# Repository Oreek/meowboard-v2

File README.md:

# ~meowpad~ Meowboard
A custom keyboard made with 62 keys and a rotary encoder. Used Kicad for the Schematics and PCB and also used OnShape for the Bottom Case.

---
## DEVLOGS
[DAY 1] Initial setup: ~creating a hackpad in EasyEDA~ Changed my mind, creating an entire 62 key keyboard.

0 hours

[DAY 1] Created complete schematic for the meowboard. Working on the PCB starting now.

2hr 30 mins
---

[DAY 1] Finally finished creating the PCB including the route tracing.

2hr 45mins
---

[DAY 1] Uhh so ig this is it. I've created the bottom plate for the PCB in onshape. Yeah, I did not make a top plate and didn't add any mounting holes because I wanted to hot glue the pcb to the bottom plate and i find the top plate pretty useless (personal preference ig)

1 hr 15 mins
---

With this, I think I'm done with the designing part of the project..? the rest I can only do with the hardware itself.

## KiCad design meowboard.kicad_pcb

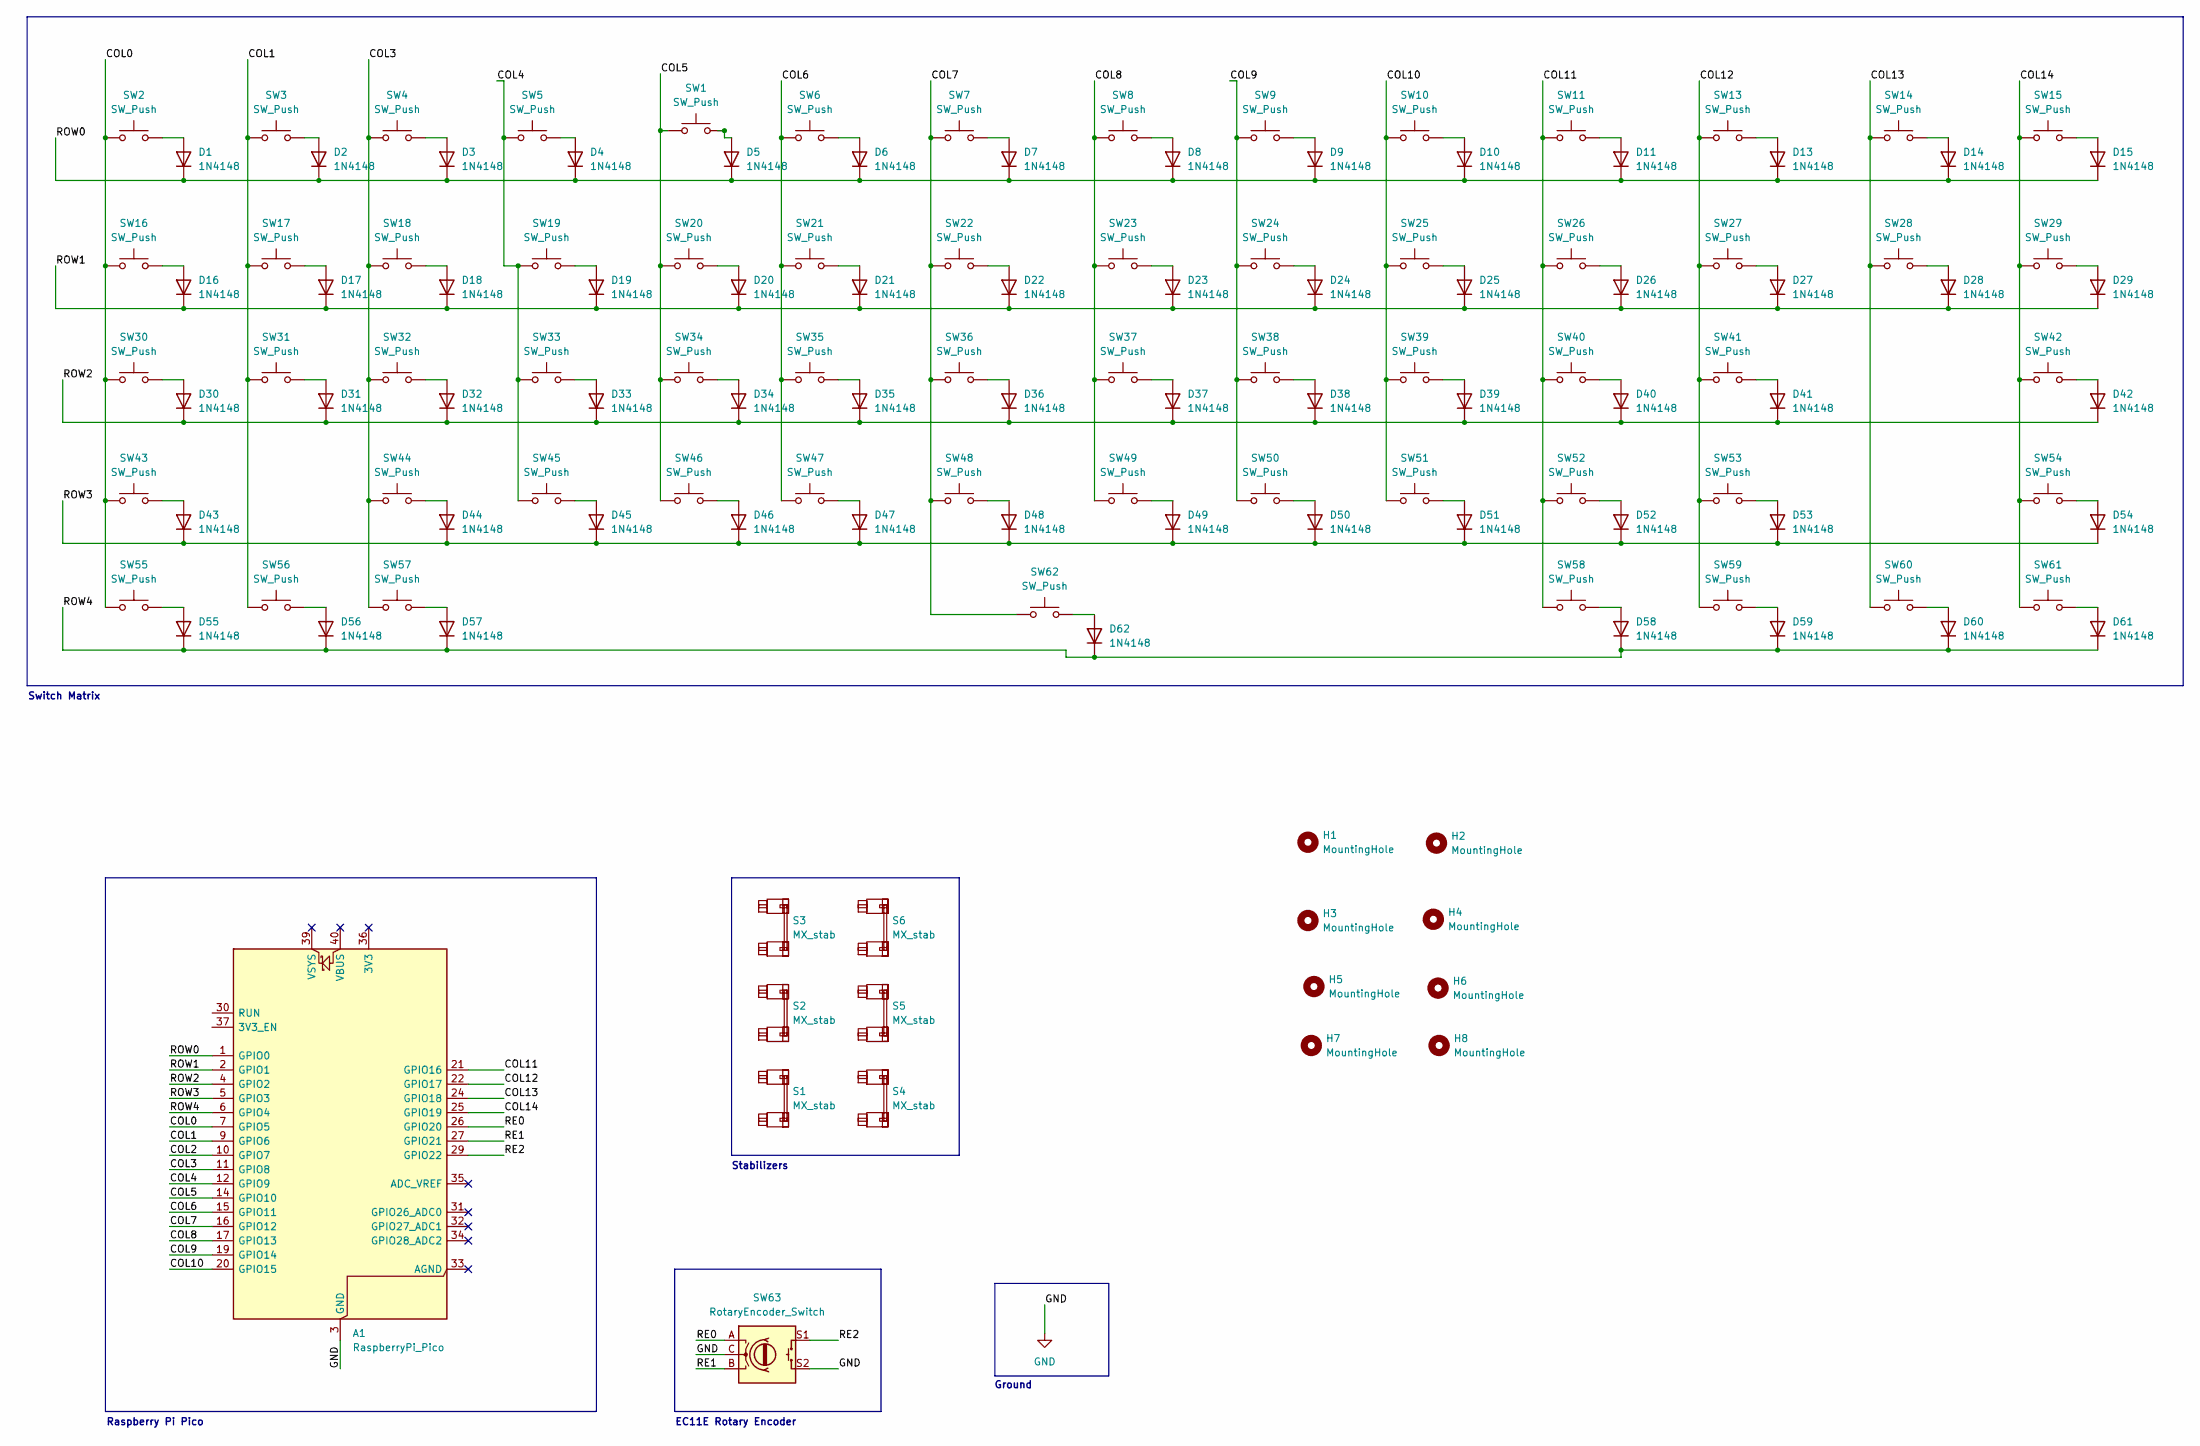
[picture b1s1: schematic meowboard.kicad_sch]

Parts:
A1: RaspberryPi_Pico; RaspberryPi_Pico_Common_Unspecified
D1, D2, D3, D4, D5, D6, D7, D8, D9, D10, D11, D13, D14, D15, D16, D17, D18, D19, D20, D21, D22, D23, D24, D25, D26, D27, D28, D29, D30, D31, D32, D33, D34, D35, D36, D37, D38, D39, D40, D41, D42, D43, D44, D45, D46, D47, D48, D49, D50, D51, D52, D53, D54, D55, D56, D57, D58, D59, D60, D61, D62: 1N4148; D_DO-35_SOD27_P7.62mm_Horizontal
H1, H2, H3, H4, H5, H6, H7, H8: MountingHole
S1, S2, S3, S4, S5, S6: MX_stab; STAB_MX_P_6.25u
SW1, SW2, SW3, SW4, SW5, SW6, SW7, SW8, SW9, SW10, SW11, SW13, SW14, SW15, SW16, SW17, SW18, SW19, SW20, SW21, SW22, SW23, SW24, SW25, SW26, SW27, SW28, SW29, SW30, SW31, SW32, SW33, SW34, SW35, SW36, SW37, SW38, SW39, SW40, SW41, SW42, SW43, SW44, SW45, SW46, SW47, SW48, SW49, SW50, SW51, SW52, SW53, SW54, SW55, SW56, SW57, SW58, SW59, SW60, SW61, SW62: SW_Push
SW63: RotaryEncoder_Switch

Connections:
/COL0: A1.7 (GPIO5), SW2.1, SW16.1, SW30.1, SW43.1, SW55.1
/COL1: A1.9 (GPIO6), SW3.1, SW17.1, SW31.1, SW56.1
/COL2: A1.10 (GPIO7)
/COL3: A1.11 (GPIO8), SW4.1, SW18.1, SW32.1, SW44.1, SW57.1
/COL4: A1.12 (GPIO9), SW5.1, SW19.1, SW33.1, SW45.1
/COL5: A1.14 (GPIO10), SW1.1, SW20.1, SW34.1, SW46.1
/COL6: A1.15 (GPIO11), SW6.1, SW21.1, SW35.1, SW47.1
/COL7: A1.16 (GPIO12), SW7.1, SW22.1, SW36.1, SW48.1, SW62.1
/COL8: A1.17 (GPIO13), SW8.1, SW23.1, SW37.1, SW49.1
/COL9: A1.19 (GPIO14), SW9.1, SW24.1, SW38.1, SW50.1
/COL10: A1.20 (GPIO15), SW10.1, SW25.1, SW39.1, SW51.1
/COL11: A1.21 (GPIO16), SW11.1, SW26.1, SW40.1, SW52.1, SW58.1
/COL12: A1.22 (GPIO17), SW13.1, SW27.1, SW41.1, SW53.1, SW59.1
/COL13: A1.24 (GPIO18), SW14.1, SW28.1, SW60.1
/COL14: A1.25 (GPIO19), SW15.1, SW29.1, SW42.1, SW54.1, SW61.1
/RE0: A1.26 (GPIO20), SW63.A
/RE1: A1.27 (GPIO21), SW63.B
/RE2: A1.29 (GPIO22), SW63.S1
/ROW0: A1.1 (GPIO0), D1.1 (K), D2.1 (K), D3.1 (K), D4.1 (K), D5.1 (K), D6.1 (K), D7.1 (K), D8.1 (K), D9.1 (K), D10.1 (K), D11.1 (K), D13.1 (K), D14.1 (K), D15.1 (K)
/ROW1: A1.2 (GPIO1), D16.1 (K), D17.1 (K), D18.1 (K), D19.1 (K), D20.1 (K), D21.1 (K), D22.1 (K), D23.1 (K), D24.1 (K), D25.1 (K), D26.1 (K), D27.1 (K), D28.1 (K), D29.1 (K)
/ROW2: A1.4 (GPIO2), D30.1 (K), D31.1 (K), D32.1 (K), D33.1 (K), D34.1 (K), D35.1 (K), D36.1 (K), D37.1 (K), D38.1 (K), D39.1 (K), D40.1 (K), D41.1 (K), D42.1 (K)
/ROW3: A1.5 (GPIO3), D43.1 (K), D44.1 (K), D45.1 (K), D46.1 (K), D47.1 (K), D48.1 (K), D49.1 (K), D50.1 (K), D51.1 (K), D52.1 (K), D53.1 (K), D54.1 (K)
/ROW4: A1.6 (GPIO4), D55.1 (K), D56.1 (K), D57.1 (K), D58.1 (K), D59.1 (K), D60.1 (K), D61.1 (K), D62.1 (K)
GND: A1.3 (GND), A1.8 (GND), A1.13 (GND), A1.18 (GND), A1.23 (GND), A1.28 (GND), A1.38 (GND), SW63.C, SW63.S2
unnamed: D1.2 (A), SW2.2
unnamed: D2.2 (A), SW3.2
unnamed: D3.2 (A), SW4.2
unnamed: D4.2 (A), SW5.2
unnamed: D5.2 (A), SW1.2
unnamed: D6.2 (A), SW6.2
unnamed: D7.2 (A), SW7.2
unnamed: D8.2 (A), SW8.2
unnamed: D9.2 (A), SW9.2
unnamed: D10.2 (A), SW10.2
unnamed: D11.2 (A), SW11.2
unnamed: D13.2 (A), SW13.2
unnamed: D14.2 (A), SW14.2
unnamed: D15.2 (A), SW15.2
unnamed: D16.2 (A), SW16.2
unnamed: D17.2 (A), SW17.2
unnamed: D18.2 (A), SW18.2
unnamed: D19.2 (A), SW19.2
unnamed: D20.2 (A), SW20.2
unnamed: D21.2 (A), SW21.2
unnamed: D22.2 (A), SW22.2
unnamed: D23.2 (A), SW23.2
unnamed: D24.2 (A), SW24.2
unnamed: D25.2 (A), SW25.2
unnamed: D26.2 (A), SW26.2
unnamed: D27.2 (A), SW27.2
unnamed: D28.2 (A), SW28.2
unnamed: D29.2 (A), SW29.2
unnamed: D30.2 (A), SW30.2
unnamed: D31.2 (A), SW31.2
unnamed: D32.2 (A), SW32.2
unnamed: D33.2 (A), SW33.2
unnamed: D34.2 (A), SW34.2
unnamed: D35.2 (A), SW35.2
unnamed: D36.2 (A), SW36.2
unnamed: D37.2 (A), SW37.2
unnamed: D38.2 (A), SW38.2
unnamed: D39.2 (A), SW39.2
unnamed: D40.2 (A), SW40.2
unnamed: D41.2 (A), SW41.2
unnamed: D42.2 (A), SW42.2
unnamed: D43.2 (A), SW43.2
unnamed: D44.2 (A), SW44.2
unnamed: D45.2 (A), SW45.2
unnamed: D46.2 (A), SW46.2
unnamed: D47.2 (A), SW47.2
unnamed: D48.2 (A), SW48.2
unnamed: D49.2 (A), SW49.2
unnamed: D50.2 (A), SW50.2
unnamed: D51.2 (A), SW51.2
unnamed: D52.2 (A), SW52.2
unnamed: D53.2 (A), SW53.2
unnamed: D54.2 (A), SW54.2
unnamed: D55.2 (A), SW55.2
unnamed: D56.2 (A), SW56.2
unnamed: D57.2 (A), SW57.2
unnamed: D58.2 (A), SW58.2
unnamed: D59.2 (A), SW59.2
unnamed: D60.2 (A), SW60.2
unnamed: D61.2 (A), SW61.2
unnamed: D62.2 (A), SW62.2

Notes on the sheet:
Switch Matrix
EC11E Rotary Encoder
Stabilizers
Raspberry Pi Pico
Ground

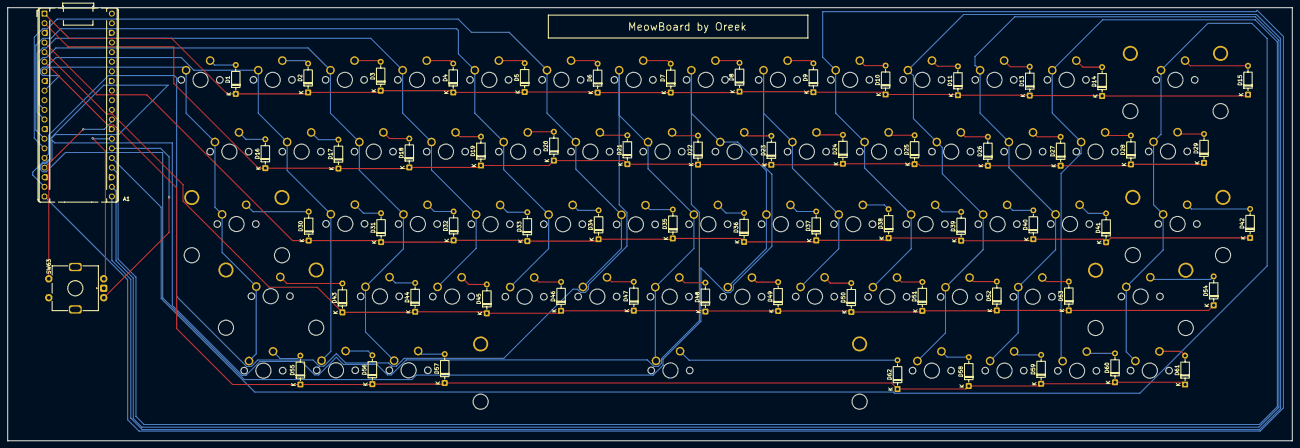
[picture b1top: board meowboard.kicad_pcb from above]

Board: 2 copper layers, 339.0 x 114.3 mm, 130 parts (0 on the bottom side), 84 nets.
